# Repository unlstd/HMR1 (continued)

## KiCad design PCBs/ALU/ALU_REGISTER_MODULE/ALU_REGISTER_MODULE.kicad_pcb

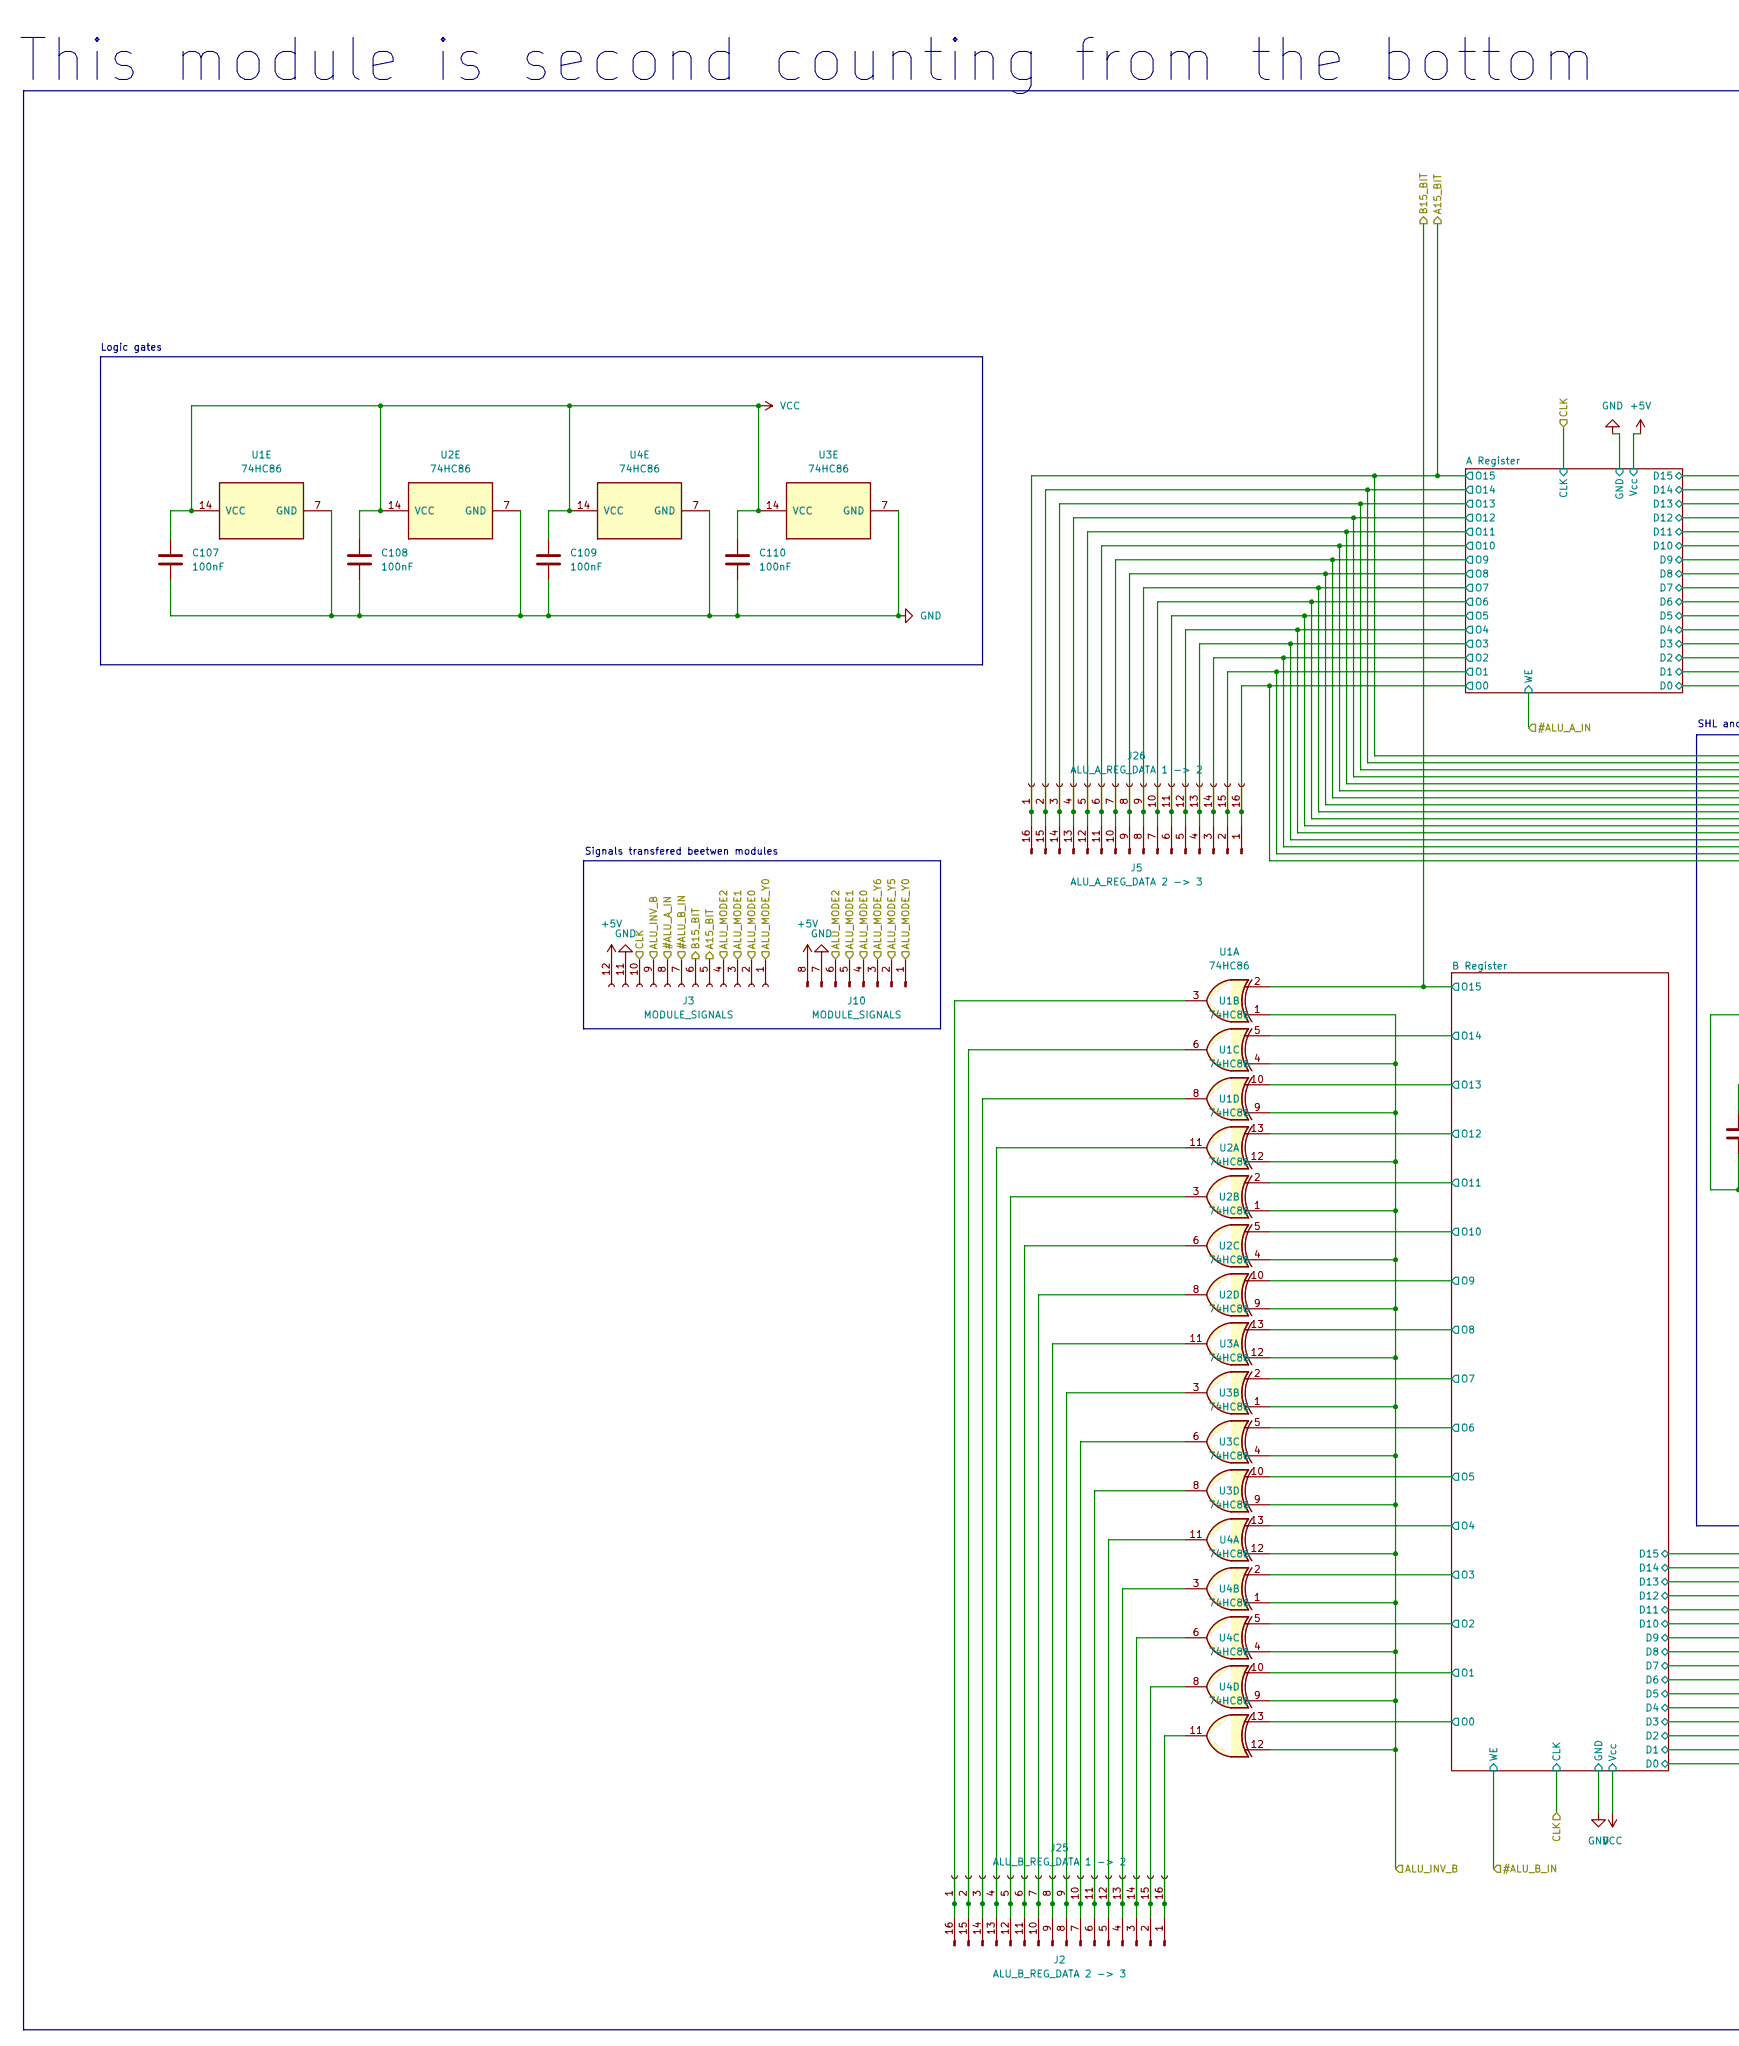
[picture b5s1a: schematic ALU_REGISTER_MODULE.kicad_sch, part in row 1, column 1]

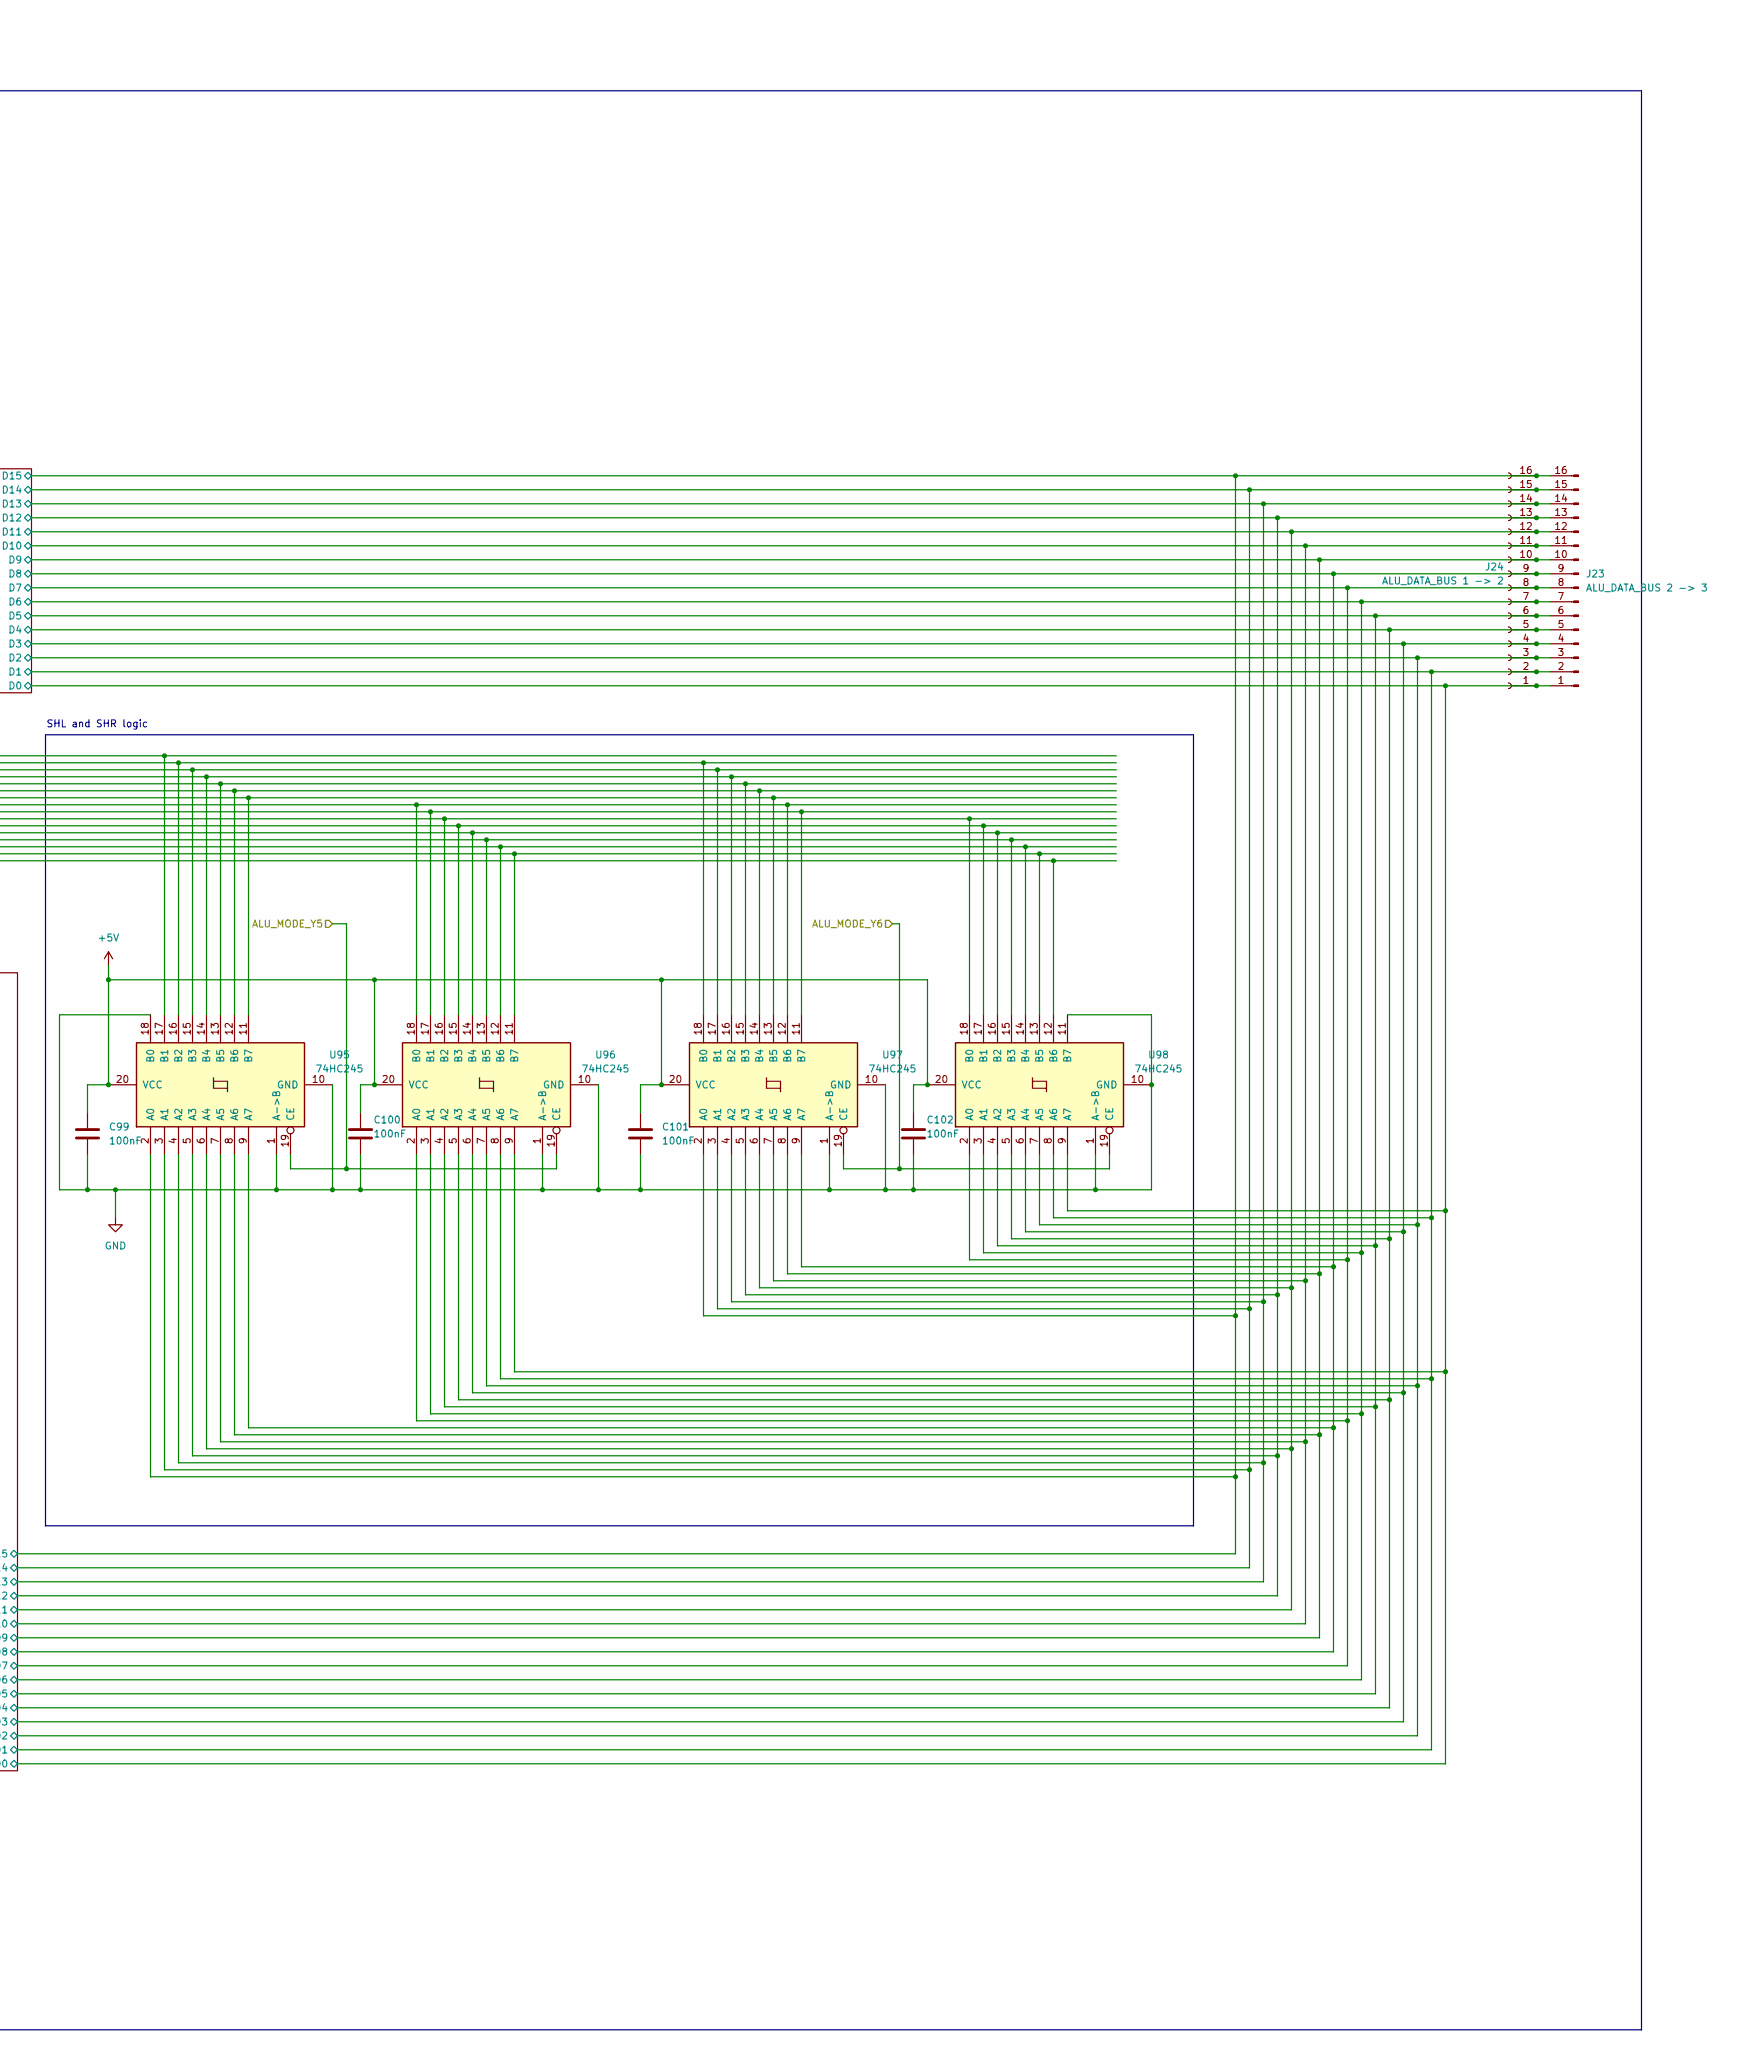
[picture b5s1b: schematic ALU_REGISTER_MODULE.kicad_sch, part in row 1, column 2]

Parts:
C99, C100, C101, C102, C107, C108, C109, C110: 100nF; C_Disc_D3.0mm_W1.6mm_P2.50mm
J2: ALU_B_REG_DATA 2 -> 3; PinHeader_1x16_P2.54mm_Vertical
J3: MODULE_SIGNALS; PinSocket_1x12_P2.54mm_Vertical
J5: ALU_A_REG_DATA 2 -> 3; PinHeader_1x16_P2.54mm_Vertical
J10: MODULE_SIGNALS; PinHeader_1x08_P2.54mm_Vertical
J23: ALU_DATA_BUS 2 -> 3; PinHeader_1x16_P2.54mm_Vertical
J24: ALU_DATA_BUS 1 -> 2; PinSocket_1x16_P2.54mm_Vertical
J25: ALU_B_REG_DATA 1 -> 2; PinSocket_1x16_P2.54mm_Vertical
J26: ALU_A_REG_DATA 1 -> 2; PinSocket_1x16_P2.54mm_Vertical
U1, U2, U3, U4: 74HC86; DIP-14_W7.62mm_Socket_LongPads
U95, U96, U97, U98: 74HC245; DIP-20_W7.62mm_Socket_LongPads

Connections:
+5V: C99.1, C100.1, C101.1, C102.1, J3.12, J10.8, U95.20 (VCC), U96.20 (VCC), U97.20 (VCC), U98.20 (VCC); also elsewhere on the board
/#ALU_A_IN: J3.8; also elsewhere on the board
/#ALU_B_IN: J3.7; also elsewhere on the board
/A15_BIT: J3.5, J5.16, J26.1, U95.17 (B1); also elsewhere on the board
/A Register/D0: J23.1, J24.1, U96.9 (A7), U98.9 (A7); also elsewhere on the board
/A Register/D1: J23.2, J24.2, U96.8 (A6), U98.8 (A6); also elsewhere on the board
/A Register/D2: J23.3, J24.3, U96.7 (A5), U98.7 (A5); also elsewhere on the board
/A Register/D3: J23.4, J24.4, U96.6 (A4), U98.6 (A4); also elsewhere on the board
/A Register/D4: J23.5, J24.5, U96.5 (A3), U98.5 (A3); also elsewhere on the board
/A Register/D5: J23.6, J24.6, U96.4 (A2), U98.4 (A2); also elsewhere on the board
/A Register/D6: J23.7, J24.7, U96.3 (A1), U98.3 (A1); also elsewhere on the board
/A Register/D7: J23.8, J24.8, U96.2 (A0), U98.2 (A0); also elsewhere on the board
/A Register/D8: J23.9, J24.9, U95.9 (A7), U97.9 (A7); also elsewhere on the board
/A Register/D9: J23.10, J24.10, U95.8 (A6), U97.8 (A6); also elsewhere on the board
/A Register/D10: J23.11, J24.11, U95.7 (A5), U97.7 (A5); also elsewhere on the board
/A Register/D11: J23.12, J24.12, U95.6 (A4), U97.6 (A4); also elsewhere on the board
/A Register/D12: J23.13, J24.13, U95.5 (A3), U97.5 (A3); also elsewhere on the board
/A Register/D13: J23.14, J24.14, U95.4 (A2), U97.4 (A2); also elsewhere on the board
/A Register/D14: J23.15, J24.15, U95.3 (A1), U97.3 (A1); also elsewhere on the board
/A Register/D15: J23.16, J24.16, U95.2 (A0), U97.2 (A0); also elsewhere on the board
/A Register/O0: J5.1, J26.16, U98.12 (B6); also elsewhere on the board
/A Register/O1: J5.2, J26.15, U96.11 (B7), U98.13 (B5); also elsewhere on the board
/A Register/O2: J5.3, J26.14, U96.12 (B6), U98.14 (B4); also elsewhere on the board
/A Register/O3: J5.4, J26.13, U96.13 (B5), U98.15 (B3); also elsewhere on the board
/A Register/O4: J5.5, J26.12, U96.14 (B4), U98.16 (B2); also elsewhere on the board
/A Register/O5: J5.6, J26.11, U96.15 (B3), U98.17 (B1); also elsewhere on the board
/A Register/O6: J5.7, J26.10, U96.16 (B2), U98.18 (B0); also elsewhere on the board
/A Register/O7: J5.8, J26.9, U96.17 (B1), U97.11 (B7); also elsewhere on the board
/A Register/O8: J5.9, J26.8, U96.18 (B0), U97.12 (B6); also elsewhere on the board
/A Register/O9: J5.10, J26.7, U95.11 (B7), U97.13 (B5); also elsewhere on the board
/A Register/O10: J5.11, J26.6, U95.12 (B6), U97.14 (B4); also elsewhere on the board
/A Register/O11: J5.12, J26.5, U95.13 (B5), U97.15 (B3); also elsewhere on the board
/A Register/O12: J5.13, J26.4, U95.14 (B4), U97.16 (B2); also elsewhere on the board
/A Register/O13: J5.14, J26.3, U95.15 (B3), U97.17 (B1); also elsewhere on the board
/A Register/O14: J5.15, J26.2, U95.16 (B2), U97.18 (B0); also elsewhere on the board
/ALU_INV_B: J3.9, U1.1, U1.4, U1.9, U1.12, U2.1, U2.4, U2.9, U2.12, U3.1, U3.4, U3.9, U3.12, U4.1, U4.4, U4.9, U4.12
/ALU_MODE0: J3.2, J10.4
/ALU_MODE1: J3.3, J10.5
/ALU_MODE2: J3.4, J10.6
/ALU_MODE_Y0: J3.1, J10.1
/ALU_MODE_Y5: J10.2, U95.19 (CE), U96.19 (CE)
/ALU_MODE_Y6: J10.3, U97.19 (CE), U98.19 (CE)
/B15_BIT: J3.6, U1.2; also elsewhere on the board
/B Register/O0: U4.13; also elsewhere on the board
/B Register/O1: U4.10; also elsewhere on the board
/B Register/O2: U4.5; also elsewhere on the board
/B Register/O3: U4.2; also elsewhere on the board
/B Register/O4: U3.13; also elsewhere on the board
/B Register/O5: U3.10; also elsewhere on the board
/B Register/O6: U3.5; also elsewhere on the board
/B Register/O7: U3.2; also elsewhere on the board
/B Register/O8: U2.13; also elsewhere on the board
/B Register/O9: U2.10; also elsewhere on the board
/B Register/O10: U2.5; also elsewhere on the board
/B Register/O11: U2.2; also elsewhere on the board
/B Register/O12: U1.13; also elsewhere on the board
/B Register/O13: U1.10; also elsewhere on the board
/B Register/O14: U1.5; also elsewhere on the board
/CLK: J3.10; also elsewhere on the board
GND: C99.2, C100.2, C101.2, C102.2, C107.2, C108.2, C109.2, C110.2, J3.11, J10.7, U1.7 (GND), U2.7 (GND), U3.7 (GND), U4.7 (GND), U95.1 (A->B), U95.10 (GND), U95.18 (B0), U96.1 (A->B), U96.10 (GND), U97.1 (A->B), U97.10 (GND), U98.1 (A->B), U98.10 (GND), U98.11 (B7); also elsewhere on the board
unnamed: J2.1, J25.16, U4.11
unnamed: J2.2, J25.15, U4.8
unnamed: J2.3, J25.14, U4.6
unnamed: J2.4, J25.13, U4.3
unnamed: J2.5, J25.12, U3.11
unnamed: J2.6, J25.11, U3.8
unnamed: J2.7, J25.10, U3.6
unnamed: J2.8, J25.9, U3.3
unnamed: J2.9, J25.8, U2.11
unnamed: J2.10, J25.7, U2.8
unnamed: J2.11, J25.6, U2.6
unnamed: J2.12, J25.5, U2.3
unnamed: J2.13, J25.4, U1.11
unnamed: J2.14, J25.3, U1.8
unnamed: J2.15, J25.2, U1.6
unnamed: J2.16, J25.1, U1.3
VCC: C107.1, C108.1, C109.1, C110.1, U1.14 (VCC), U2.14 (VCC), U3.14 (VCC), U4.14 (VCC); also elsewhere on the board

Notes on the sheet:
Logic gates
SHL and SHR logic
Signals transfered beetwen modules
This module is second counting from the bottom

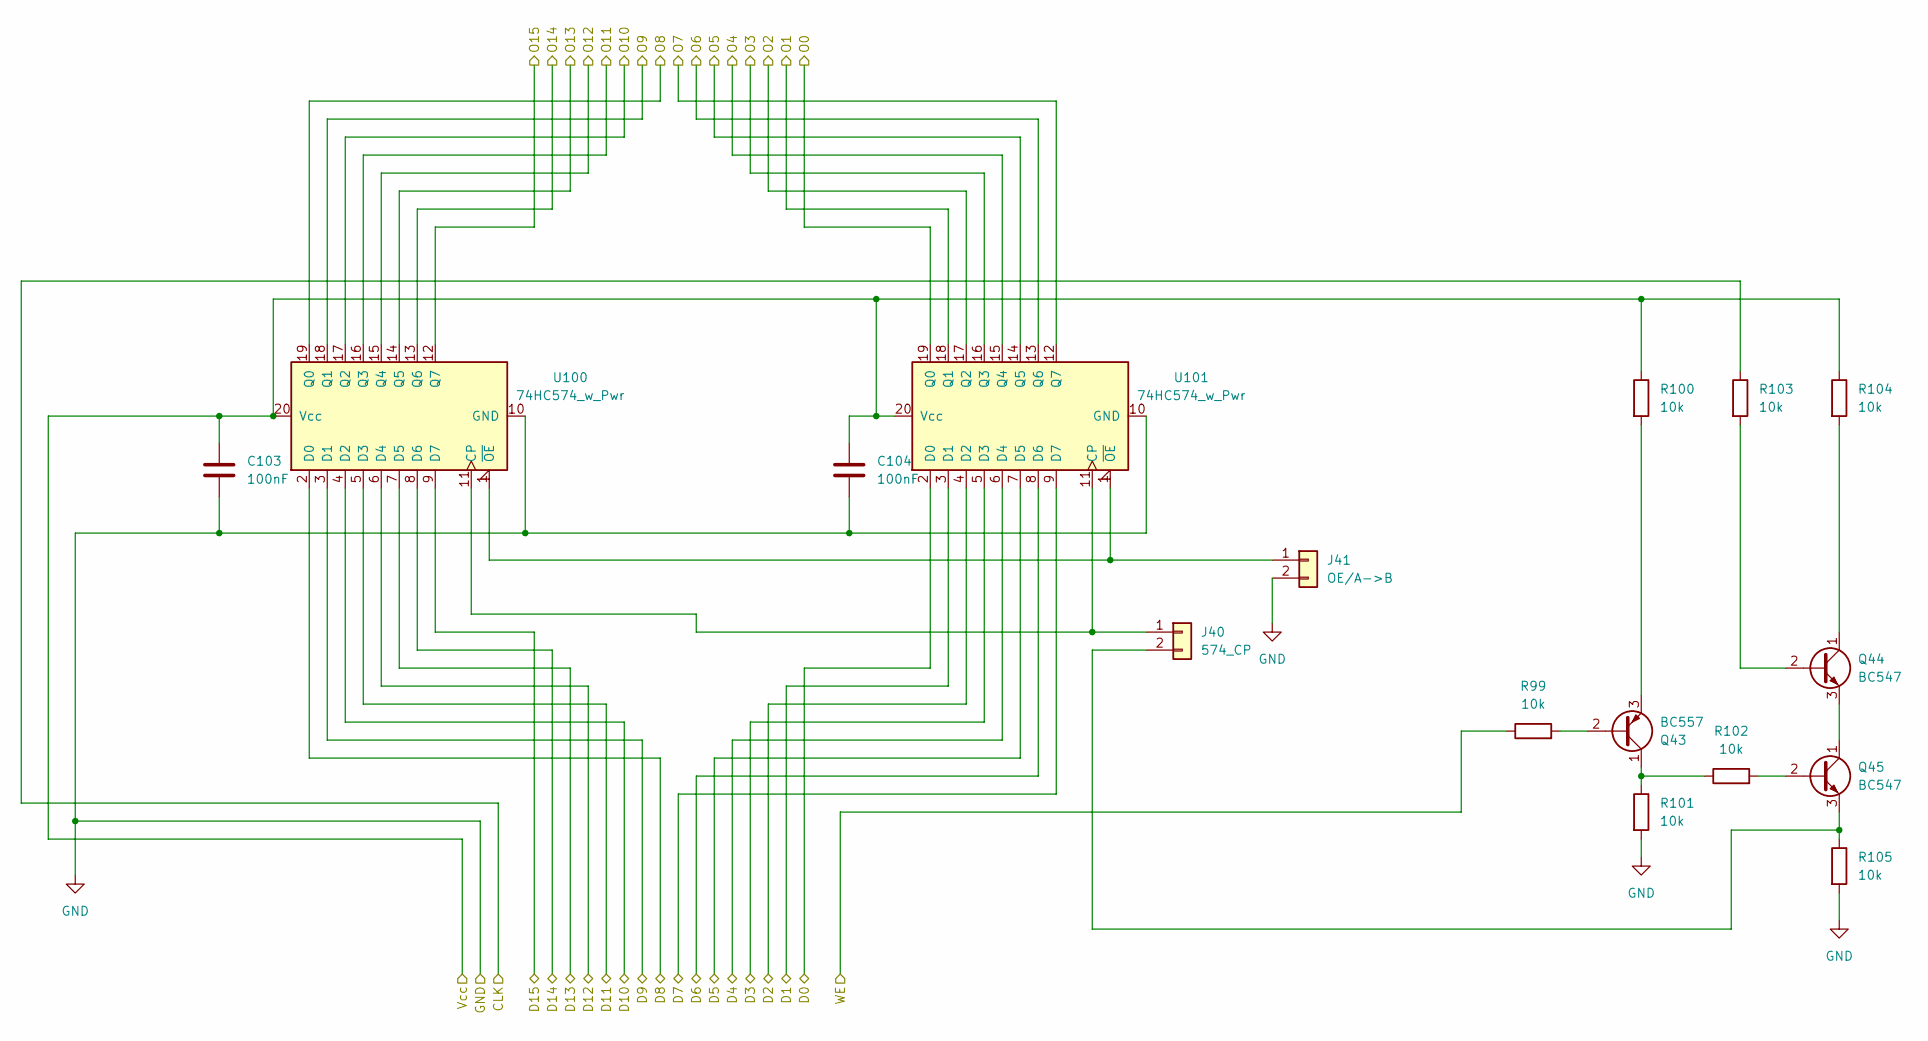
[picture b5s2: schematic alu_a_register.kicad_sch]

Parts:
C103, C104: 100nF; C_Disc_D3.0mm_W1.6mm_P2.50mm
J40: 574_CP; PinHeader_1x02_P2.54mm_Horizontal
J41: OE/A->B; PinHeader_1x02_P2.54mm_Horizontal
Q43: BC557; TO-92_Inline
Q44, Q45: BC547; TO-92_Inline
R99, R100, R101, R102, R103, R104, R105: 10k; R_Axial_DIN0207_L6.3mm_D2.5mm_P10.16mm_Horizontal
U100, U101: 74HC574_w_Pwr; DIP-20_W7.62mm_Socket_LongPads

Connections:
+5V: C103.1, C104.1, R100.1, R104.1, U100.20 (Vcc), U101.20 (Vcc); also elsewhere on the board
/#ALU_A_IN: R99.1; also elsewhere on the board
/A15_BIT: U100.12 (Q7); also elsewhere on the board
/A Register/D0: U101.2 (D0); also elsewhere on the board
/A Register/D1: U101.3 (D1); also elsewhere on the board
/A Register/D2: U101.4 (D2); also elsewhere on the board
/A Register/D3: U101.5 (D3); also elsewhere on the board
/A Register/D4: U101.6 (D4); also elsewhere on the board
/A Register/D5: U101.7 (D5); also elsewhere on the board
/A Register/D6: U101.8 (D6); also elsewhere on the board
/A Register/D7: U101.9 (D7); also elsewhere on the board
/A Register/D8: U100.2 (D0); also elsewhere on the board
/A Register/D9: U100.3 (D1); also elsewhere on the board
/A Register/D10: U100.4 (D2); also elsewhere on the board
/A Register/D11: U100.5 (D3); also elsewhere on the board
/A Register/D12: U100.6 (D4); also elsewhere on the board
/A Register/D13: U100.7 (D5); also elsewhere on the board
/A Register/D14: U100.8 (D6); also elsewhere on the board
/A Register/D15: U100.9 (D7); also elsewhere on the board
/A Register/O0: U101.19 (Q0); also elsewhere on the board
/A Register/O1: U101.18 (Q1); also elsewhere on the board
/A Register/O2: U101.17 (Q2); also elsewhere on the board
/A Register/O3: U101.16 (Q3); also elsewhere on the board
/A Register/O4: U101.15 (Q4); also elsewhere on the board
/A Register/O5: U101.14 (Q5); also elsewhere on the board
/A Register/O6: U101.13 (Q6); also elsewhere on the board
/A Register/O7: U101.12 (Q7); also elsewhere on the board
/A Register/O8: U100.19 (Q0); also elsewhere on the board
/A Register/O9: U100.18 (Q1); also elsewhere on the board
/A Register/O10: U100.17 (Q2); also elsewhere on the board
/A Register/O11: U100.16 (Q3); also elsewhere on the board
/A Register/O12: U100.15 (Q4); also elsewhere on the board
/A Register/O13: U100.14 (Q5); also elsewhere on the board
/A Register/O14: U100.13 (Q6); also elsewhere on the board
/CLK: R103.1; also elsewhere on the board
GND: C103.2, C104.2, J41.2, R101.2, R105.2, U100.10 (GND), U101.10 (GND); also elsewhere on the board
unnamed: J40.1, U100.11 (CP), U101.11 (CP)
unnamed: J40.2, Q45.3 (E), R105.1
unnamed: J41.1, U100.1 (~OE), U101.1 (~OE)
unnamed: Q43.2 (B), R99.2
unnamed: Q43.1 (C), R101.1, R102.1
unnamed: Q43.3 (E), R100.2
unnamed: Q44.2 (B), R103.2
unnamed: Q44.1 (C), R104.2
unnamed: Q44.3 (E), Q45.1 (C)
unnamed: Q45.2 (B), R102.2

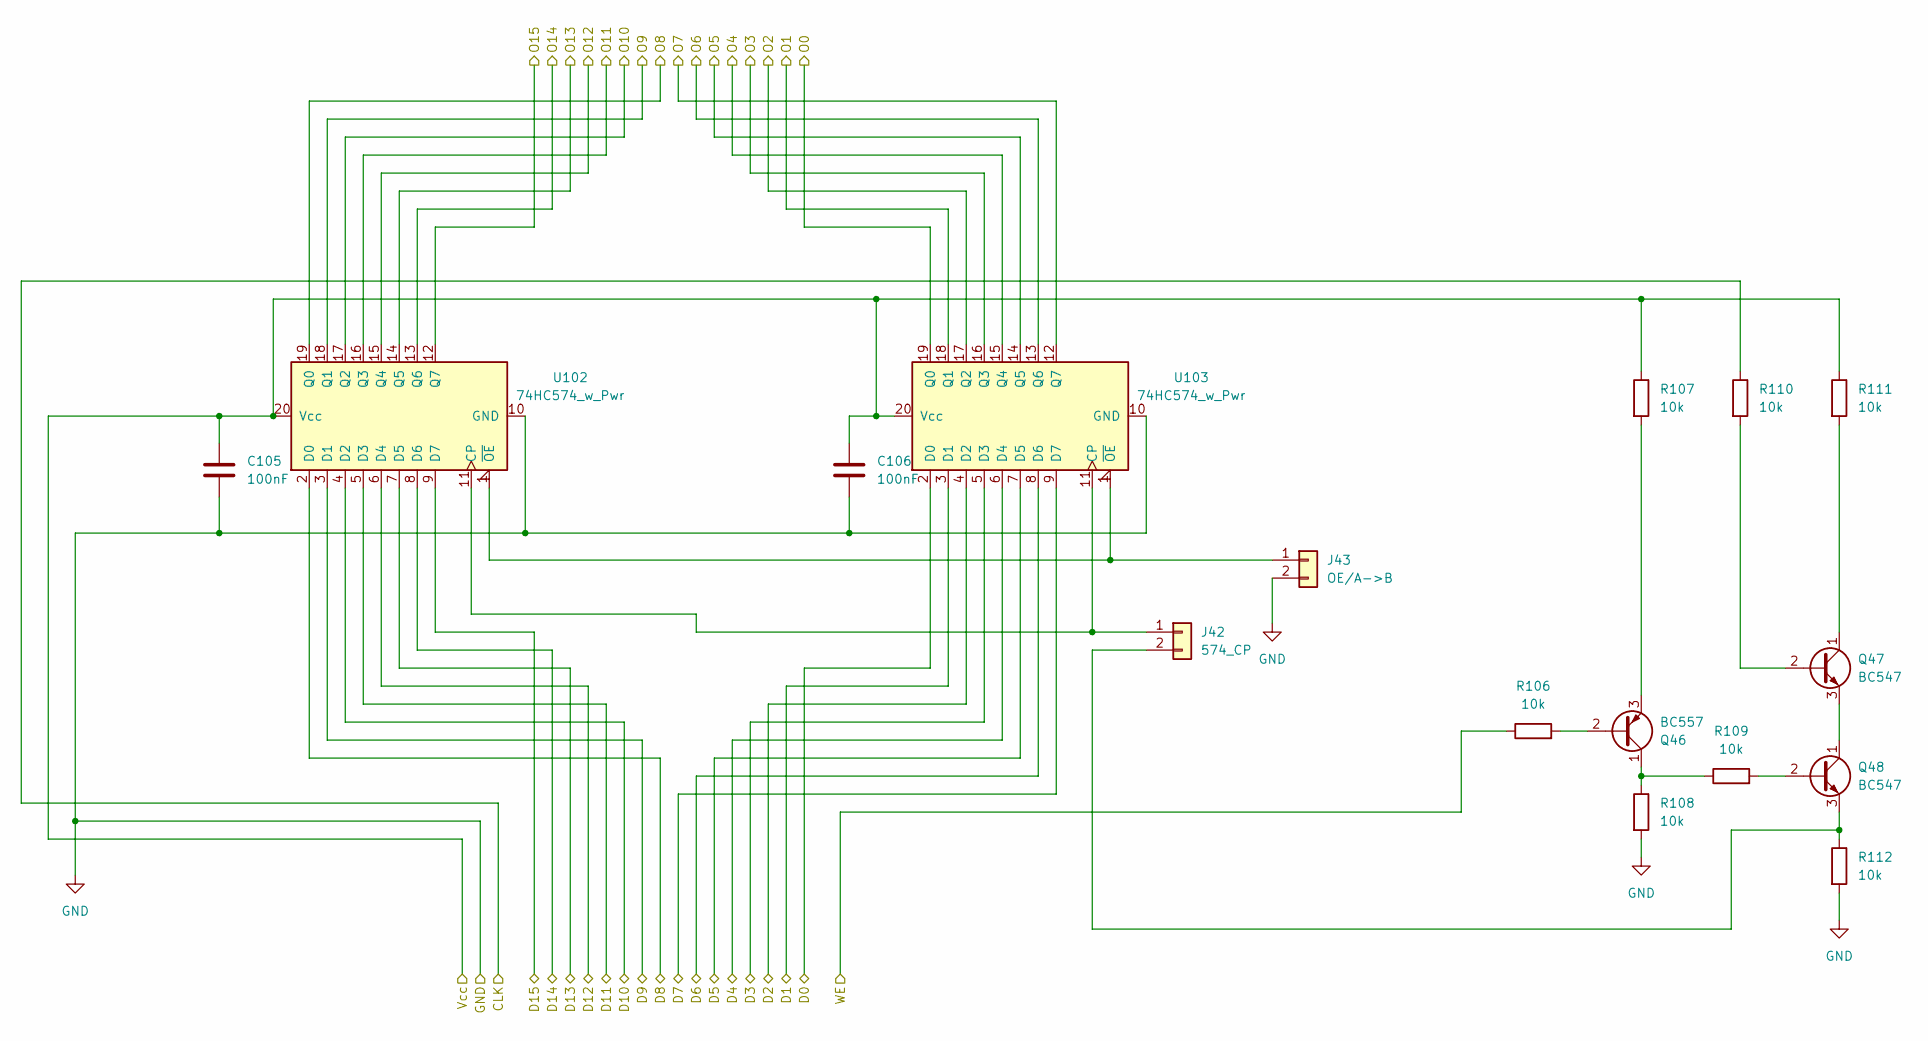
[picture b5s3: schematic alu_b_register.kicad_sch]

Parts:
C105, C106: 100nF; C_Disc_D3.0mm_W1.6mm_P2.50mm
J42: 574_CP; PinHeader_1x02_P2.54mm_Horizontal
J43: OE/A->B; PinHeader_1x02_P2.54mm_Horizontal
Q46: BC557; TO-92_Inline
Q47, Q48: BC547; TO-92_Inline
R106, R107, R108, R109, R110, R111, R112: 10k; R_Axial_DIN0207_L6.3mm_D2.5mm_P10.16mm_Horizontal
U102, U103: 74HC574_w_Pwr; DIP-20_W7.62mm_Socket_LongPads

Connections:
/#ALU_B_IN: R106.1; also elsewhere on the board
/A Register/D0: U103.2 (D0); also elsewhere on the board
/A Register/D1: U103.3 (D1); also elsewhere on the board
/A Register/D2: U103.4 (D2); also elsewhere on the board
/A Register/D3: U103.5 (D3); also elsewhere on the board
/A Register/D4: U103.6 (D4); also elsewhere on the board
/A Register/D5: U103.7 (D5); also elsewhere on the board
/A Register/D6: U103.8 (D6); also elsewhere on the board
/A Register/D7: U103.9 (D7); also elsewhere on the board
/A Register/D8: U102.2 (D0); also elsewhere on the board
/A Register/D9: U102.3 (D1); also elsewhere on the board
/A Register/D10: U102.4 (D2); also elsewhere on the board
/A Register/D11: U102.5 (D3); also elsewhere on the board
/A Register/D12: U102.6 (D4); also elsewhere on the board
/A Register/D13: U102.7 (D5); also elsewhere on the board
/A Register/D14: U102.8 (D6); also elsewhere on the board
/A Register/D15: U102.9 (D7); also elsewhere on the board
/B15_BIT: U102.12 (Q7); also elsewhere on the board
/B Register/O0: U103.19 (Q0); also elsewhere on the board
/B Register/O1: U103.18 (Q1); also elsewhere on the board
/B Register/O2: U103.17 (Q2); also elsewhere on the board
/B Register/O3: U103.16 (Q3); also elsewhere on the board
/B Register/O4: U103.15 (Q4); also elsewhere on the board
/B Register/O5: U103.14 (Q5); also elsewhere on the board
/B Register/O6: U103.13 (Q6); also elsewhere on the board
/B Register/O7: U103.12 (Q7); also elsewhere on the board
/B Register/O8: U102.19 (Q0); also elsewhere on the board
/B Register/O9: U102.18 (Q1); also elsewhere on the board
/B Register/O10: U102.17 (Q2); also elsewhere on the board
/B Register/O11: U102.16 (Q3); also elsewhere on the board
/B Register/O12: U102.15 (Q4); also elsewhere on the board
/B Register/O13: U102.14 (Q5); also elsewhere on the board
/B Register/O14: U102.13 (Q6); also elsewhere on the board
/CLK: R110.1; also elsewhere on the board
GND: C105.2, C106.2, J43.2, R108.2, R112.2, U102.10 (GND), U103.10 (GND); also elsewhere on the board
unnamed: J42.1, U102.11 (CP), U103.11 (CP)
unnamed: J42.2, Q48.3 (E), R112.1
unnamed: J43.1, U102.1 (~OE), U103.1 (~OE)
unnamed: Q46.2 (B), R106.2
unnamed: Q46.1 (C), R108.1, R109.1
unnamed: Q46.3 (E), R107.2
unnamed: Q47.2 (B), R110.2
unnamed: Q47.1 (C), R111.2
unnamed: Q47.3 (E), Q48.1 (C)
unnamed: Q48.2 (B), R109.2
VCC: C105.1, C106.1, R107.1, R111.1, U102.20 (Vcc), U103.20 (Vcc); also elsewhere on the board

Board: 2 copper layers, 56 parts (0 on the bottom side), 97 nets, no tracks yet.

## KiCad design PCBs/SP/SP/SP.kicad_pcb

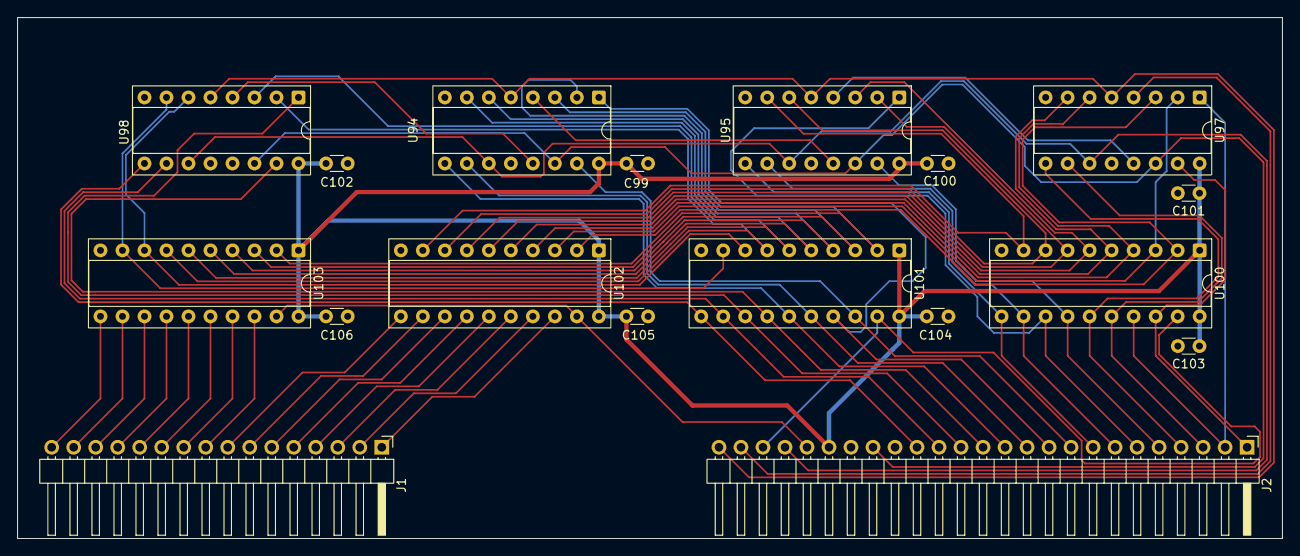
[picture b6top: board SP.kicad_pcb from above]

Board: 2 copper layers, 146.0 x 60.1 mm, 18 parts (0 on the bottom side), 59 nets.

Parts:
C99, C100, C101, C102, C103, C104, C105, C106: 100nF; C_Disc_D3.0mm_W1.6mm_P2.50mm
J1: Conn_01x16_Pin; PinHeader_1x16_P2.54mm_Horizontal
J2: Conn_01x25_Pin; PinHeader_1x25_P2.54mm_Horizontal
U94, U95, U97, U98: 74LS191; DIP-16_W7.62mm_Socket
U100, U101, U102, U103: 74HC245; DIP-20_W7.62mm_Socket

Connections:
+5V: C99.1, C100.1, C101.1, C102.1, C103.1, C104.1, C105.1, C106.1, J2.20, U94.16 (VCC), U95.16 (VCC), U97.16 (VCC), U98.16 (VCC), U100.1 (A->B), U100.20 (VCC), U101.1 (A->B), U101.20 (VCC), U102.1 (A->B), U102.20 (VCC), U103.1 (A->B), U103.20 (VCC)
/#SP_ADDR_OUT: J2.21, U102.19 (CE), U103.19 (CE)
/#SP_COUNT_EN: J2.24, U97.4 (Ce)
/#SP_DATA_IN: J2.22, U94.11 (Pl), U95.11 (Pl), U97.11 (Pl), U98.11 (Pl)
/#SP_DATA_OUT: J2.23, U100.19 (CE), U101.19 (CE)
/#SP_DIRECTION: J2.25, U94.5 (D/U), U95.5 (D/U), U97.5 (D/U), U98.5 (D/U)
/A0: J1.1, U102.18 (B0)
/A1: J1.2, U102.17 (B1)
/A2: J1.3, U102.16 (B2)
/A3: J1.4, U102.15 (B3)
/A4: J1.5, U102.14 (B4)
/A5: J1.6, U102.13 (B5)
/A6: J1.7, U102.12 (B6)
/A7: J1.8, U102.11 (B7)
/A8: J1.9, U103.18 (B0)
/A9: J1.10, U103.17 (B1)
/A10: J1.11, U103.16 (B2)
/A11: J1.12, U103.15 (B3)
/A12: J1.13, U103.14 (B4)
/A13: J1.14, U103.13 (B5)
/A14: J1.15, U103.12 (B6)
/A15: J1.16, U103.11 (B7)
/CLK: J2.18, U94.14 (Cp), U95.14 (Cp), U97.14 (Cp), U98.14 (Cp)
/D0: J2.1, U97.15 (P0), U100.18 (B0)
/D1: J2.2, U97.1, U100.17 (B1)
/D2: J2.3, U97.10 (P2), U100.16 (B2)
/D3: J2.4, U97.9 (P3), U100.15 (B3)
/D4: J2.5, U95.15 (P0), U100.14 (B4)
/D5: J2.6, U95.1, U100.13 (B5)
/D6: J2.7, U95.10 (P2), U100.12 (B6)
/D7: J2.8, U95.9 (P3), U100.11 (B7)
/D8: J2.9, U94.15 (P0), U101.18 (B0)
/D9: J2.10, U94.1, U101.17 (B1)
/D10: J2.11, U94.10 (P2), U101.16 (B2)
/D11: J2.12, U94.9 (P3), U101.15 (B3)
/D12: J2.13, U98.15 (P0), U101.14 (B4)
/D13: J2.14, U98.1, U101.13 (B5)
/D14: J2.15, U98.10 (P2), U101.12 (B6)
/D15: J2.16, U98.9 (P3), U101.11 (B7)
GND: C99.2, C100.2, C101.2, C102.2, C103.2, C104.2, C105.2, C106.2, J2.19, U94.8 (GND), U95.8 (GND), U97.8 (GND), U98.8 (GND), U100.10 (GND), U101.10 (GND), U102.10 (GND), U103.10 (GND)
unnamed: U94.4 (Ce), U95.13 (Rc)
unnamed: U94.13 (Rc), U98.4 (Ce)
unnamed: U95.4 (Ce), U97.13 (Rc)
unnamed: U97.3 (Q0), U100.2 (A0), U102.2 (A0)
unnamed: U97.2 (Q1), U100.3 (A1), U102.3 (A1)
unnamed: U97.6 (Q2), U100.4 (A2), U102.4 (A2)
unnamed: U97.7 (Q3), U100.5 (A3), U102.5 (A3)
unnamed: U95.3 (Q0), U100.6 (A4), U102.6 (A4)
unnamed: U95.2 (Q1), U100.7 (A5), U102.7 (A5)
unnamed: U95.6 (Q2), U100.8 (A6), U102.8 (A6)
unnamed: U95.7 (Q3), U100.9 (A7), U102.9 (A7)
unnamed: U94.3 (Q0), U101.2 (A0), U103.2 (A0)
unnamed: U94.2 (Q1), U101.3 (A1), U103.3 (A1)
unnamed: U94.6 (Q2), U101.4 (A2), U103.4 (A2)
unnamed: U94.7 (Q3), U101.5 (A3), U103.5 (A3)
unnamed: U98.3 (Q0), U101.6 (A4), U103.6 (A4)
unnamed: U98.2 (Q1), U101.7 (A5), U103.7 (A5)
unnamed: U98.6 (Q2), U101.8 (A6), U103.8 (A6)
unnamed: U98.7 (Q3), U101.9 (A7), U103.9 (A7)
